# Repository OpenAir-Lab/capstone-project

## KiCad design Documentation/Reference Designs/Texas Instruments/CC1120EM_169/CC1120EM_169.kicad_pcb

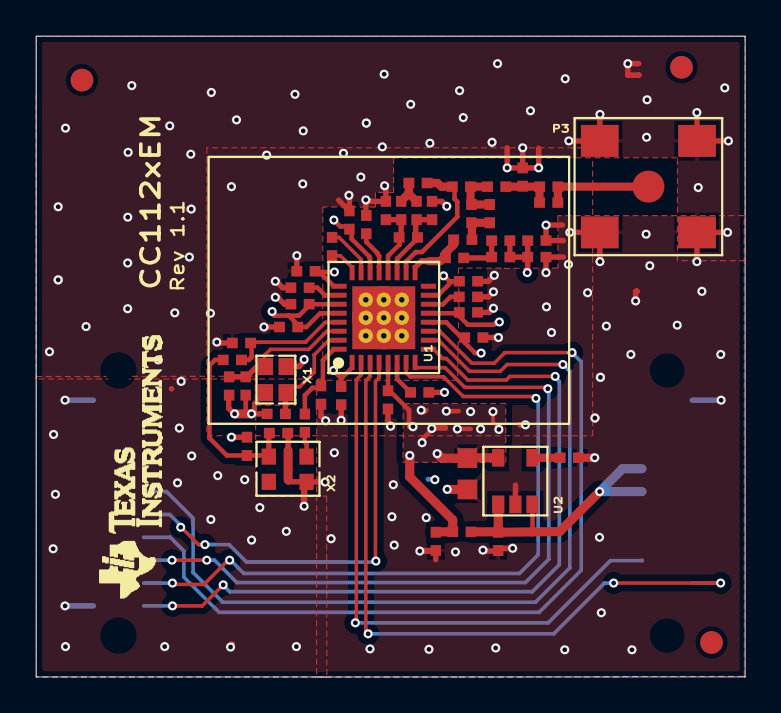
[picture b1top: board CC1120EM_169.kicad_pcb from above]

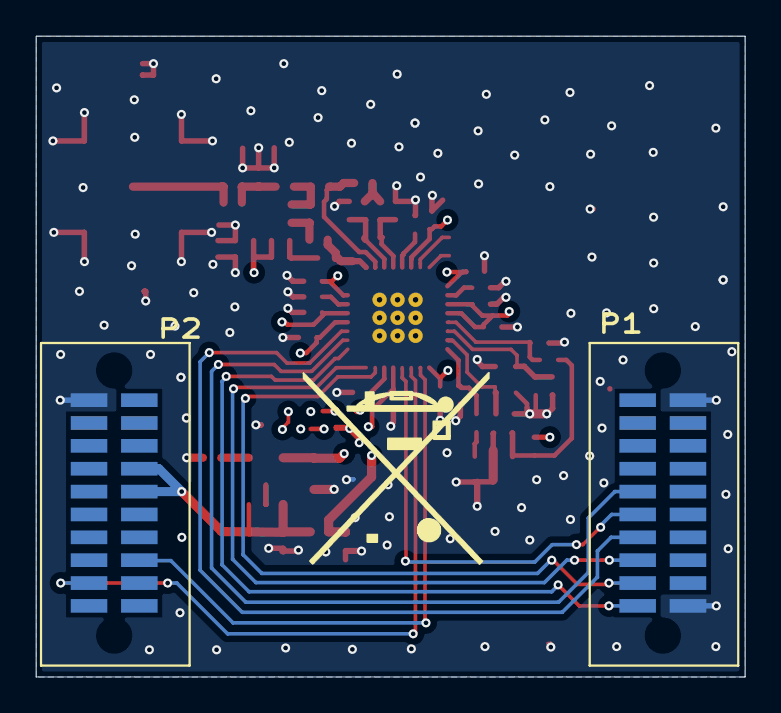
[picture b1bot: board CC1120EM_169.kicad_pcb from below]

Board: 4 copper layers, 39.4 x 35.6 mm, 57 parts (2 on the bottom side), 34 nets.

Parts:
C11, C51, C121, C131, C151, C221, C251, C261, C271, C281, C291: C_47N_0402_X7R_K_25; 0402 (REFLOW LF)
C12, C321: C_100N_0402_X5R_K_10; 0402 (REFLOW LF)
C41, C171, C211: C_10N_0402_X7R_K_25; 0402 (REFLOW LF)
C52: C_2U2_0603_X5R_K_10; 0603 (REFLOW)
C53, C302: C_0402; 0402 (REFLOW LF)
C61: C_220N_0402_X5R_K_10; 0402 (REFLOW LF)
C172, C173: C_100P_0402_NP0_J_50; 0402 (REFLOW LF)
C174: C_82P_0402_NP0_J_50; 0402 (REFLOW LF)
C175, C301, C311: C_15P_0402_NP0_J_50; 0402 (REFLOW LF)
C176, C181, C191, C201: C_12P_0402_NP0_J_50; 0402 (REFLOW LF)
C177: C_1P2_0402_NP0_B_50; 0402 (REFLOW LF)
C231: C_1N8_0402_U2J_J_10; 0402 (REFLOW LF)
C322: C_22P_0402_NP0_J_50; 0402 (REFLOW LF)
FM1, FM2, FM3: FIDUCIAL_MARK; FIDUCAL_MARK
L1: L_BEAD_102_0402; 0402 (REFLOW LF)
L171: L_220N_0402_J; 0402 (REFLOW LF)
L172: L_18N_0402_J_LQW; 0402 (REFLOW LF)
L173: L_100N_0402_J_LQW; 0402 (REFLOW LF)
L174: L_68N_0402_J_LQW; 0402 (REFLOW LF)
L191: L_150N_0402_J; 0402 (REFLOW LF)
L192, L201: L_82N_0402_J_LQW; 0402 (REFLOW LF)
L193: L_39N_0402_J_LQW; 0402 (REFLOW LF)
P1, P2: SMD_SOCKET_2X10; SFM SMD Socket 2x10
P3: SMA_SMD; SMA_SMD (Extended)
R12, R322: R_0_0402; 0402 (REFLOW LF)
R141: R_56K_0402_F; 0402 (REFLOW LF)
R171: R_22_0402_J; 0402 (REFLOW LF)
R321: R_0402; 0402 (REFLOW LF)
U1: CC112X; QFN32_RHM (DATASHEET)
U2: TPS79930; SOT23-5
X1: X_32.000/10/20/60/10; XTAL_SMD_2x1_6 (2.0x1.6mm no paste reduction)
X2: TG_5021CG; TCXO_TG_5021CG (2.5x2mm)

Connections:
3V3A: C12.1, L1.1, P2.7, P2.9, U2.1, U2.3
AGND: C11.1, C12.2, C41.2, C51.1, C52.2, C53.2, C61.2, C121.1, C131.1, C151.1, C171.2, C172.2, C175.2, C201.2, C211.2, C221.2, C251.1, C261.1, C271.1, C281.1, C291.1, C301.1, C302.1, C311.1, C321.1, L192.1, P1.1, P1.19, P2.2, P3.2, P3.3, P3.4, P3.5, R12.1, R141.2, U1.33, U2.2, X1.2, X1.4, X2.2
CSN: P1.14, U1.11
GPIO0: P1.10, U1.10
GPIO2: P1.12, U1.4
GPIO3: P2.18, U1.3
MISO: P1.20, U1.9
MOSI: P1.18, U1.7
unnamed: C41.1, U2.4
unnamed: C173.1, L171.2, R171.1
unnamed: C174.1, C176.1, L172.2
unnamed: C176.2, C181.2, L172.1, L173.2
unnamed: C201.1, L191.2, L201.2, U1.20
unnamed: C211.1, U1.21
unnamed: C231.1, U1.23
unnamed: C301.2, C302.2, U1.30, X1.3
unnamed: C322.1, X2.3
unnamed: C175.1, C177.1, L173.1, L174.2
unnamed: C191.2, L191.1, L192.2, U1.19
unnamed: C181.1, L193.1, U1.18
unnamed: C191.1, L193.2, L201.1
unnamed: C177.2, L174.1, P3.1
unnamed: C322.2, R12.2, U1.32
unnamed: C291.2, R321.2, U1.29
unnamed: C321.2, R321.1, R322.1, X2.4
unnamed: C61.1, U1.6
unnamed: R141.1, U1.14
unnamed: C174.2, L171.1, U1.17
unnamed: C231.2, U1.24
unnamed: C261.2, U1.26
unnamed: C311.2, U1.31, X1.1
RESET: P2.15, U1.2
SCLK: P1.16, U1.8
VDD_REG: C11.2, C51.2, C52.1, C53.1, C121.2, C131.2, C151.2, C171.1, C172.1, C173.2, C221.1, C251.2, C271.2, C281.2, L1.2, R171.2, R322.2, U1.1, U1.5, U1.12, U1.13, U1.15, U1.22, U1.25, U1.27, U1.28, U2.5

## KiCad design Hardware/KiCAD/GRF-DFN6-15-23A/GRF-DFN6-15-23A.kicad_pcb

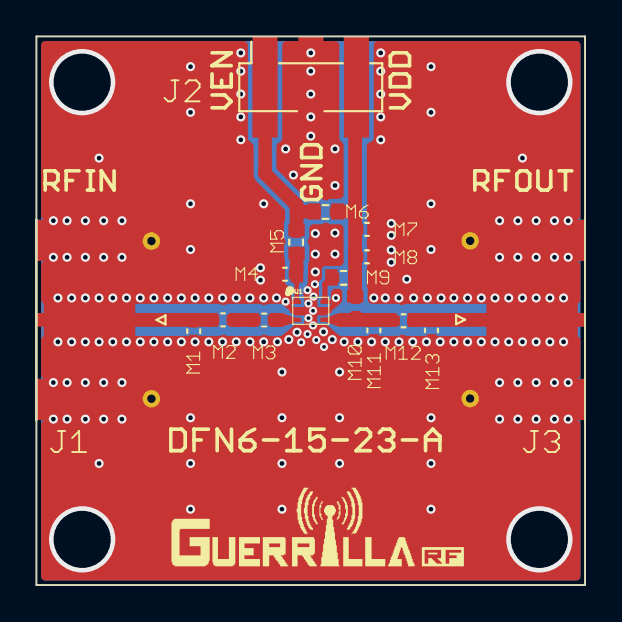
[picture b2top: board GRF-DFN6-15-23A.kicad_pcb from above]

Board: 4 copper layers, 30.5 x 30.5 mm, 21 parts (0 on the bottom side), 10 nets.

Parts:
FID0: GRF_LOCAL_FIDUCIAL; Fiducial_0.5mm_Mask1.5mm
FID@1: GRF_LOCAL_FIDUCIAL; Fiducial_0.5mm_Mask1.5mm
J1: MOLEX_KK_HEADER_3-PIN_0.100-INCH; PinSocket_1x03_P2.54mm_Vertical_SMD_Pin1Right
M1, M11, M13: 0.5pF; C_0402_1005Metric
M2, M3, M4, M12: 100pF; C_0402_1005Metric
M5, M6, M9: 0 Ohm; R_0402_1005Metric
M7, M8: 0.1uF; C_0402_1005Metric
M10: 220nH WW; L_0402_1005Metric
RFIN0: SMA-142-0701-801/806; SMA_Molex_73251-1153_EdgeMount_Horizontal
RFOUT0: SMA-142-0701-801/806; SMA_Molex_73251-1153_EdgeMount_Horizontal
U$1: DFN-6_GENERICUPDATED; SON50P150X150X50-7N-D
U$2, U$3: GRF_LOCAL_FIDUCIAL; Fiducial_0.5mm_Mask1.5mm

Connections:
GND: J1.2, M1.2, M4.2, M7.2, M8.2, M11.2, M13.2, RFIN0.2 (Ext), RFOUT0.2 (Ext), U$1.2 (NC_1), U$1.5 (NC_2), U$1.7 (GND)
unnamed: J1.1, M5.2, M6.1
unnamed: J1.3, M6.2, M7.1, M8.1, M9.2, M10.1
unnamed: M2.2, M3.1
unnamed: M1.1, M2.1, RFIN0.1 (In)
unnamed: M12.1, M13.1, RFOUT0.1 (In)
unnamed: M9.1, U$1.6 (NC_3)
unnamed: M3.2, U$1.3 (RFIN)
unnamed: M10.2, M11.1, M12.2, U$1.4 (RFOUT/VD)
unnamed: M4.1, M5.1, U$1.1 (VEN)

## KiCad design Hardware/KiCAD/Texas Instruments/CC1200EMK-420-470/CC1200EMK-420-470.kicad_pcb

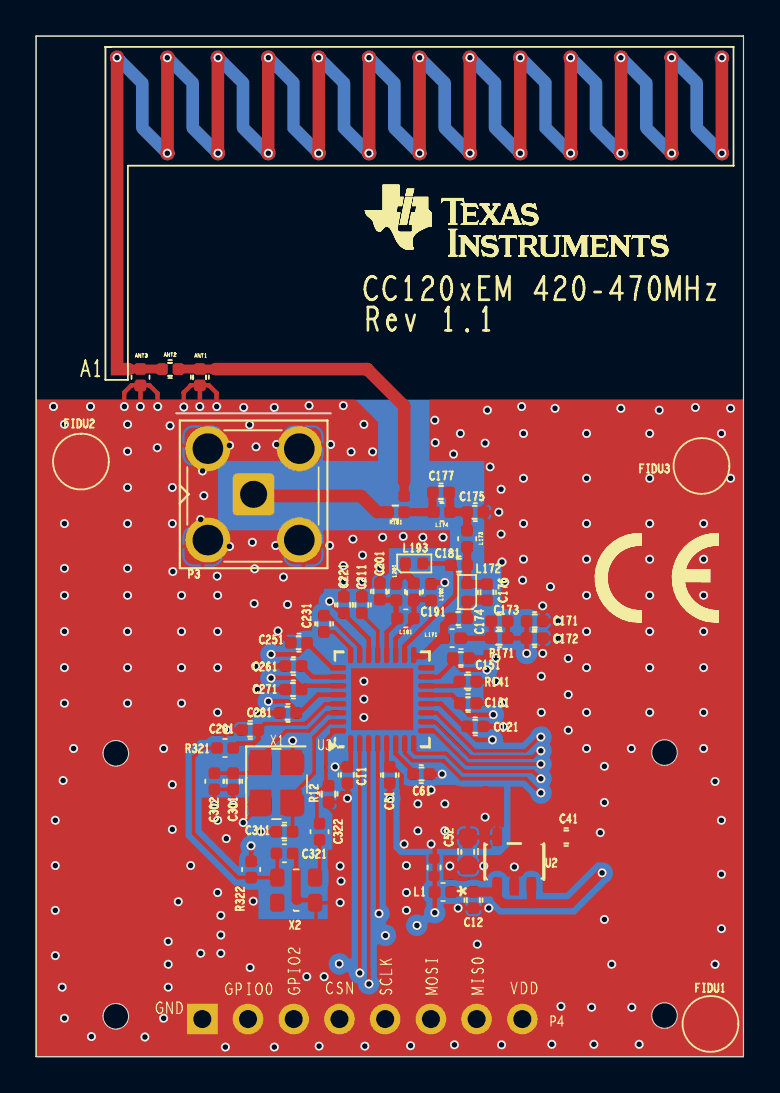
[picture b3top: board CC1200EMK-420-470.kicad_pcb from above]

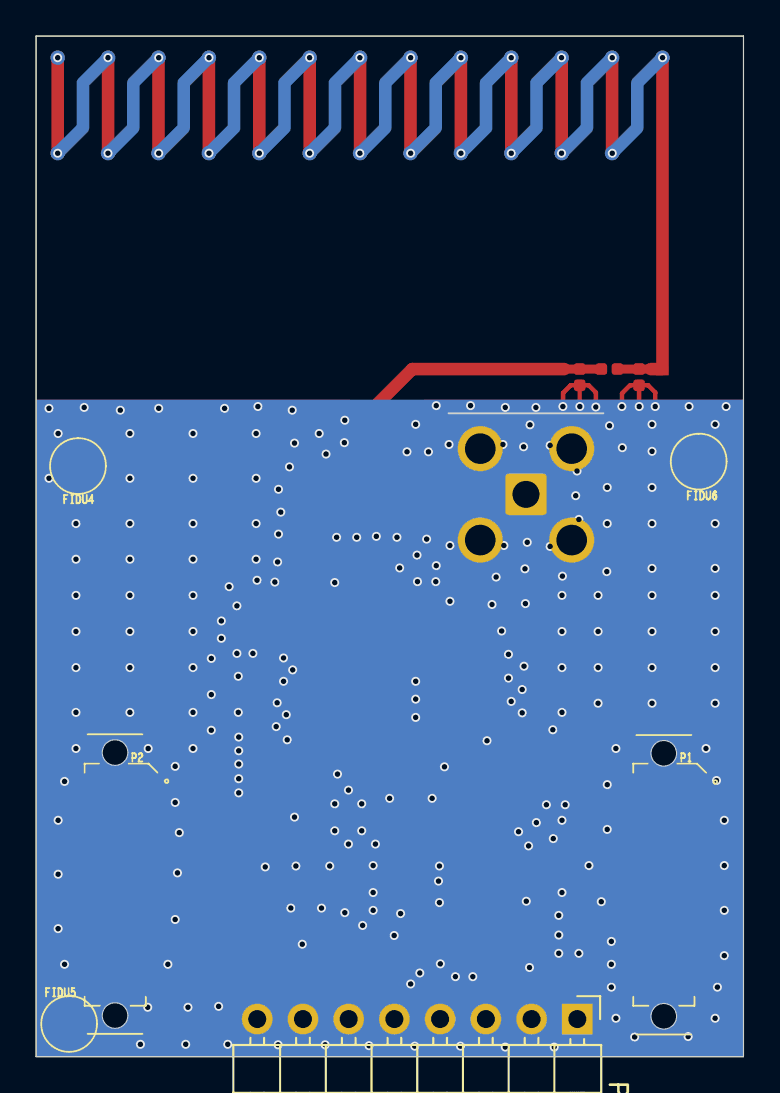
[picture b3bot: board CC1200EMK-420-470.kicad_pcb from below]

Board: 4 copper layers, 39.3 x 56.7 mm, 59 parts (6 on the bottom side), 35 nets.

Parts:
Ant1, Ant2: 0.9p; C_0402_1005Metric
Ant3: 56n; L_0402_1005Metric
C11, C51, C53, C121, C131, C151, C221, C251, C261, C271, C281, C291: 47n; C_0402_1005Metric
C12: 100n; C_0402_1005Metric
C41, C171, C211: 10n; C_0402_1005Metric
C52: 2.2u; C_0402_1005Metric
C61: 220n; C_0402_1005Metric
C172: 100p; C_0402_1005Metric
C173: 56p; C_0402_1005Metric
C174: 39p; C_0402_1005Metric
C175: 6.2p; C_0402_1005Metric
C176: 2.2p; C_0402_1005Metric
C177: 1.2p; C_0402_1005Metric
C181, C191, C201: 5.1p; C_0402_1005Metric
C231: 1.5n; C_0402_1005Metric
C301, C311: 15p; C_0402_1005Metric
FID1, FID2, FID3, FID4, FID5, FID6: Fiducial; Fiducial_1.5mm_Mask3mm
L1: BLM15HG102SN1D; L_0402_1005Metric
L171, L191: 56n; L_0402_1005Metric
L172, L193: 15n; L_0402_1005Metric
L173: 43n; L_0402_1005Metric
L174: 22n; L_0402_1005Metric
L192, L201: 27n; L_0402_1005Metric
P1, P2: SFM-110-02-S-D-A-K-TR; SFM-110-YY-XXX-D-A-K-TR
P3: Conn_Coaxial_UHF; SMA_Amphenol_901-143_Horizontal
P4: Conn_01x08; PinHeader_1x08_P2.54mm_Horizontal
R12: 0R; R_0402_1005Metric
R141: 56k; R_0402_1005Metric
R171, R181: 18; R_0402_1005Metric
U1: TPS79330-EP; DDC5_TEX
U3: CC1200RHBR; QFN-32-1EP_5x5mm_P0.5mm_EP3.45x3.45mm
X1: 40 MHz; Crystal_SMD_3225-4Pin_3.2x2.5mm

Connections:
/CC_GPIO0: P1.10, P4.2, U3.10 (GPIO0)
/CC_GPIO2: P1.12, P4.3, U3.4 (GPIO2)
/CC_GPIO3: P2.18, U3.3 (GPIO3)
/CC_MISO: P1.20, P4.7, U3.9 (SO(GPIO1))
/CC_MOSI: P1.18, P4.6, U3.7 (SI)
/CC_NCS: P1.14, P4.4, U3.11 (~CS)
/CC_NRST: P2.15, U3.2 (~RESET)
/CC_SCLK: P1.16, P4.5, U3.8 (SCLK)
/CC_X1: C301.2, U3.30 (XOSC_Q1), X1.1
/CC_X2: C311.1, U3.31 (XOSC_Q2), X1.3
/LNA_N: C201.1, L191.2, L201.1, U3.20 (LNA_N)
/LNA_P: C191.1, L191.1, L192.1, U3.19 (LNA_P)
/PA: C174.2, L171.2, U3.17 (PA)
/RF_Signal: C177.2, L174.2, R181.2
/TRX_SW: C181.2, L193.1, U3.18 (TRX_SW)
GND: Ant1.2, Ant3.2, C11.2, C12.2, C41.2, C51.2, C52.2, C53.2, C61.2, C121.2, C131.2, C151.2, C171.2, C172.2, C175.2, C201.2, C211.2, C221.2, C251.2, C261.2, C271.2, C281.2, C291.2, C301.1, C311.2, L192.2, P1.1, P1.19, P2.2, P2.20, P3.2 (Ext), P4.1, R12.1, R141.2, U1.2 (GND), U3.33 (GND_EP), X1.2, X1.4
unnamed: Ant1.1, Ant2.1
unnamed: Ant2.2, Ant3.1
unnamed: C173.2, L171.1, R171.2
unnamed: C174.1, C176.2, L172.1
unnamed: C175.1, C177.1, L173.2, L174.1
unnamed: C176.1, C181.1, L172.2, L173.1
unnamed: C191.2, L193.2, L201.2
unnamed: P3.1 (In), R181.1
unnamed: C41.1, U1.4 (FB)
unnamed: C61.1, U3.6 (DCPL)
unnamed: C261.1, U3.26 (DCPL_PFD_CHP)
unnamed: C211.1, U3.21 (DCPL_VCO)
unnamed: C291.1, U3.29 (DCPL_XOSC)
unnamed: R12.2, U3.32 (EXT_XOSC)
unnamed: C231.2, U3.23 (LPF0)
unnamed: C231.1, U3.24 (LPF1)
unnamed: R141.1, U3.14 (RBIAS)
VBUS: C12.1, L1.1, U1.1 (IN), U1.3 (EN)
VDD: C11.1, C51.1, C52.1, C53.1, C121.1, C131.1, C151.1, C171.1, C172.1, C173.1, C221.1, C251.1, C271.1, C281.1, L1.2, P2.7, P2.9, P4.8, R171.1, U1.5 (OUT), U3.1 (VDD_GUARD), U3.5 (DVDD), U3.12 (DVDD), U3.13 (AVDD_IF), U3.15 (AVDD_RF), U3.22 (AVDD_SYNTH1), U3.25 (AVDD_PFD_CHP), U3.27 (AVDD_SYNTH2), U3.28 (AVDD_XOSC)

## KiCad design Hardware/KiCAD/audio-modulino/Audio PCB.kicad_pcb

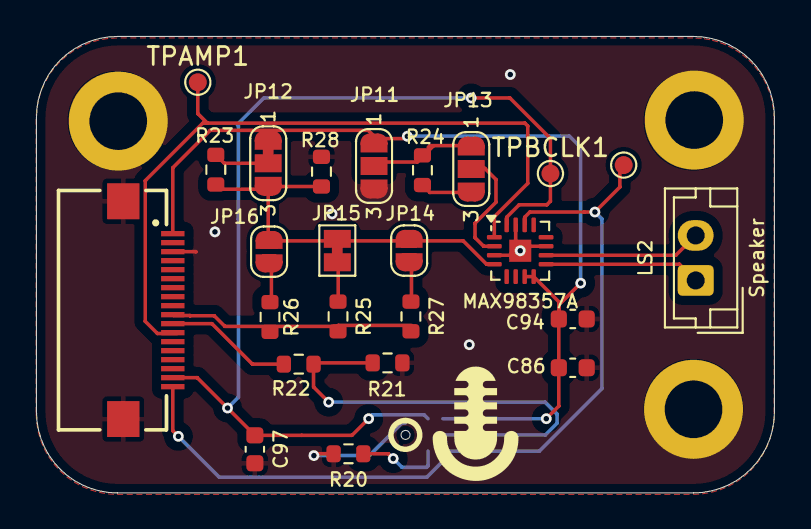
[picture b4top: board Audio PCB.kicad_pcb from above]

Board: 2 copper layers, 41.0 x 25.4 mm, 28 parts (1 on the bottom side), 19 nets.

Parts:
C86: 1uF; C_0603_1608Metric
C94: 0.1uF; C_0603_1608Metric
C97: 22pF; C_0603_1608Metric
H13, H15, H16: M3; MountingHole_3.2mm_M3_ISO14580_Pad
JP11: GAIN_{LOGIC}; SolderJumper-3_P1.3mm_Open_RoundedPad1.0x1.5mm_NumberLabels
JP12: Driver; SolderJumper-3_P1.3mm_Bridged12_RoundedPad1.0x1.5mm_NumberL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
JP13: GAIN_{R}; SolderJumper-3_P1.3mm_Open_RoundedPad1.0x1.5mm_NumberLabels
JP14: CH_LEFT; SolderJumper-2_P1.3mm_Open_RoundedPad1.0x1.5mm
JP15: CH_MONO_MIX; SolderJumper-2_P1.3mm_Bridged_Pad1.0x1.5mm
JP16: CH_RIGHT; SolderJumper-2_P1.3mm_Open_RoundedPad1.0x1.5mm
LS2: Speaker; JST_EH_B2B-EH-A_1x02_P2.50mm_Vertical
MK2: ICS-43434; InvenSense_ICS-43434-6_3.5x2.65mm
R20, R21: 47k; R_0603_1608Metric
R22: 68; R_0603_1608Metric
R23, R27: 2k; R_0603_1608Metric
R24: 100k 5%; R_0603_1608Metric
R25: 634k; R_0603_1608Metric
R26: 330k; R_0603_1608Metric
R28: 100k; R_0603_1608Metric
TPAMP1: TestPoint_Pad_D1.0mm
TPBCLK1: TestPoint_Pad_D1.0mm
TPLRCLK1: TestPoint_Pad_D1.0mm
U7: MAX98357A; TQFN-16-1EP_3x3mm_P0.5mm_EP1.23x1.23mm
X2: EYESPI; Adafruit EYESPI FPC Connector

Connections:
+3.3V: C86.1, C94.1, JP11.1 (A), JP12.1 (A), MK2.5 (VDD), U7.7 (VDD), U7.8 (VDD), X2.1
/AMP_DIN: TPAMP1.1, U7.1 (DIN), X2.12
/Audio Subsystem/GAIN_SLOT: JP13.2 (C), U7.2 (GAIN_SLOT)
/Audio Subsystem/~SD_MODE: JP12.3 (B), JP14.2 (B), JP15.2 (B), JP16.2 (B), R23.2, R28.2, U7.4 (~SD_MODE)
/BCLK: C97.1, MK2.4 (SCK), TPBCLK1.1, U7.16 (BCLK), X2.17
/LRCLK: MK2.1 (WS), TPLRCLK1.1, U7.14 (LRCLK), X2.18
/MIC_DOUT: R22.2, X2.11
/~AMP_SD: R25.2, R26.1, R27.2, X2.10
GND: C86.2, C94.2, C97.2, H13.1, H15.1, H16.1, JP11.3 (B), MK2.3 (GND), R20.2, R21.2, R28.1, U7.3 (GND), U7.11 (GND), U7.15 (GND), U7.17 (PAD), X2.3, X2.Z1, X2.Z2
unnamed: JP11.2 (C), JP13.1 (A), R24.1
unnamed: JP12.2 (C), R23.1
unnamed: JP13.3 (B), R24.2
unnamed: JP14.1 (A), R27.1
unnamed: JP15.1 (A), R25.1
unnamed: JP16.1 (A), R26.2
unnamed: MK2.2 (LR), R20.1
unnamed: MK2.6 (SD), R21.1, R22.1
unnamed: LS2.2, U7.10 (OUTN)
unnamed: LS2.1, U7.9 (OUTP)

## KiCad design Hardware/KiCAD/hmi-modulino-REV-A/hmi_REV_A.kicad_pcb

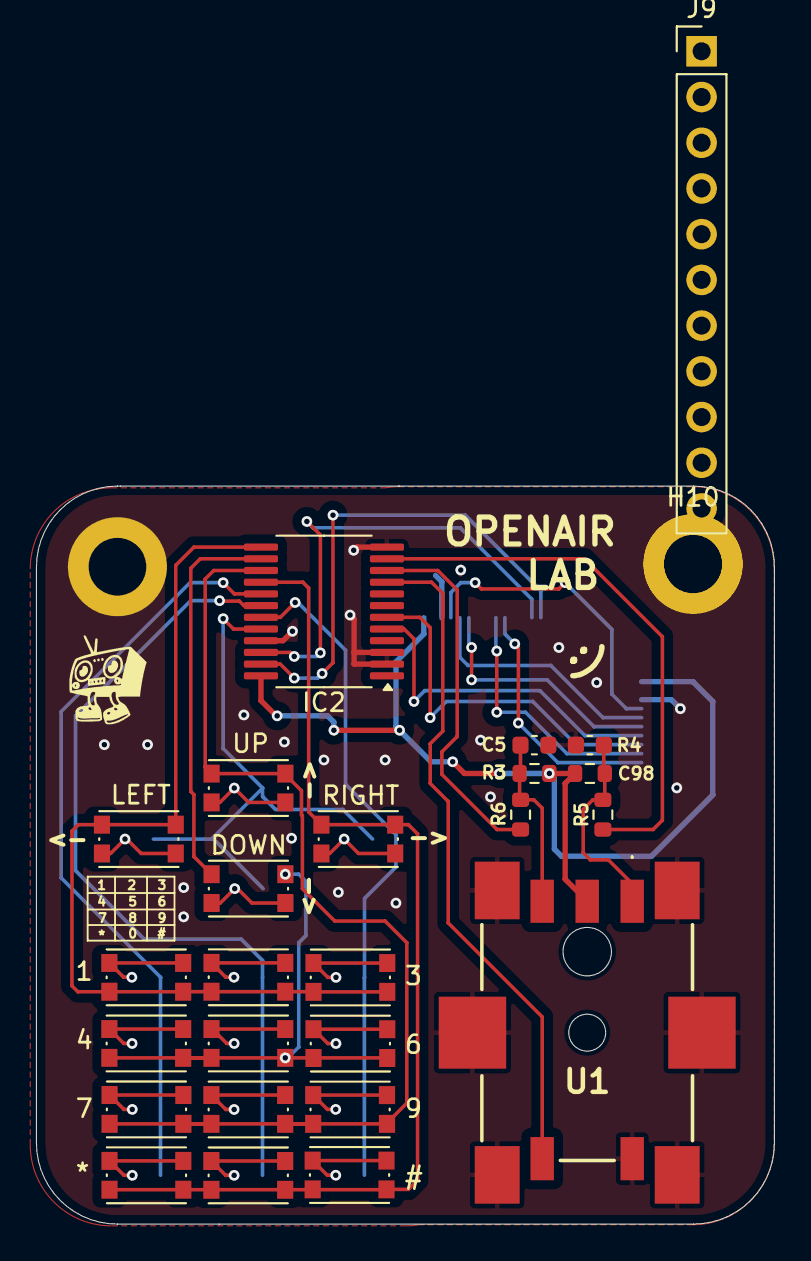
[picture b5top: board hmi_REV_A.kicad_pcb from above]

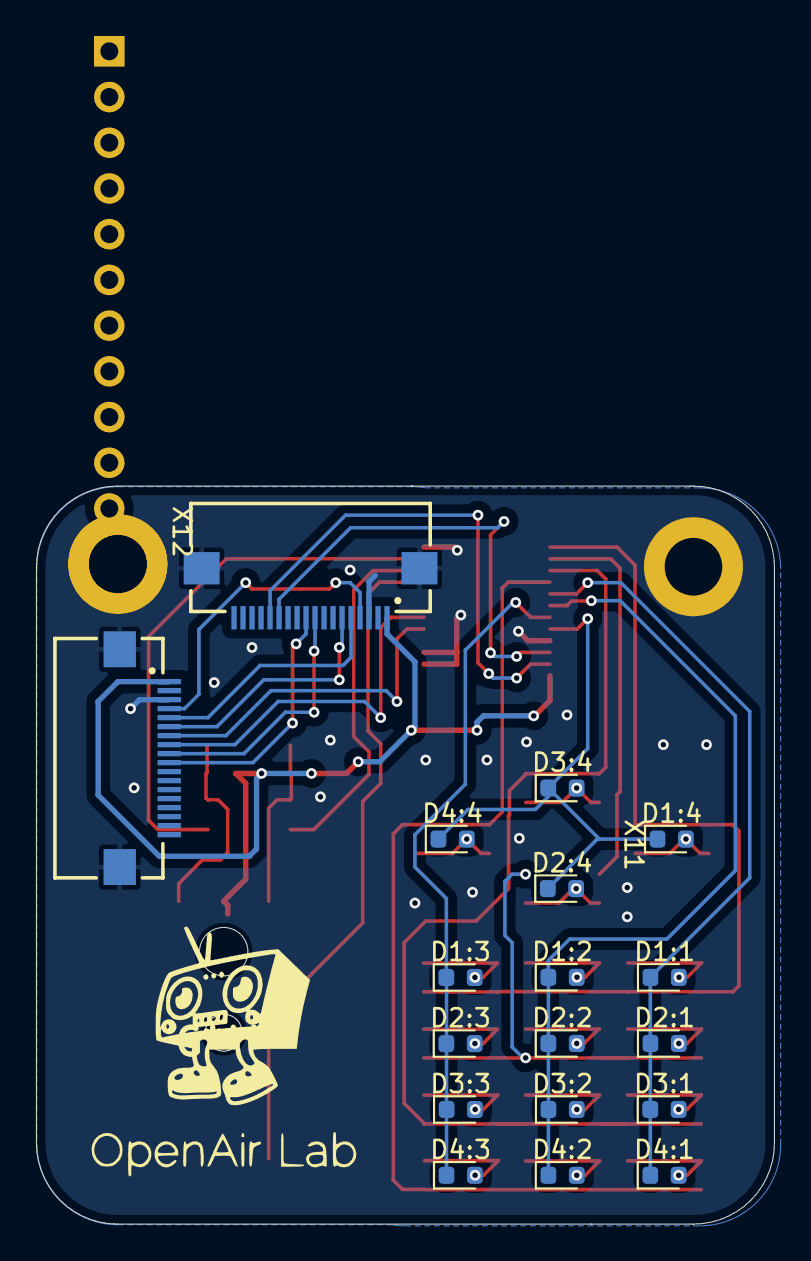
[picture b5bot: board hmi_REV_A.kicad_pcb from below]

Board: 2 copper layers, 41.0 x 41.0 mm, 46 parts (18 on the bottom side), 41 nets.

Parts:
C5, C98: 0.01uF; C_0603_1608Metric
D1:1, D1:2, D1:3, D1:4, D2:1, D2:2, D2:3, D2:4, D3:1, D3:2, D3:3, D3:4, D4:1, D4:2, D4:3, D4:4: D; D_0603_1608Metric
H3, H8, H10: M3; MountingHole_3.2mm_M3_ISO14580_Pad
IC2: PCF8575PWR; SSOP-24_5.3x8.2mm_P0.65mm
J9: Display Pin Socket; PinHeader_1x11_P2.54mm_Vertical
R3, R4, R5, R6: 10k; R_0603_1608Metric
SW30: #; SW_Push_1P1T_NO_CK_KMR2
SW31: 1; SW_Push_1P1T_NO_CK_KMR2
SW32: 4; SW_Push_1P1T_NO_CK_KMR2
SW33: 7; SW_Push_1P1T_NO_CK_KMR2
SW34: 0; SW_Push_1P1T_NO_CK_KMR2
SW35: 2; SW_Push_1P1T_NO_CK_KMR2
SW36: 5; SW_Push_1P1T_NO_CK_KMR2
SW37: 8; SW_Push_1P1T_NO_CK_KMR2
SW38: *; SW_Push_1P1T_NO_CK_KMR2
SW39: 3; SW_Push_1P1T_NO_CK_KMR2
SW40: 6; SW_Push_1P1T_NO_CK_KMR2
SW41: 9; SW_Push_1P1T_NO_CK_KMR2
SW42: RIGHT; SW_Push_1P1T_NO_CK_KMR2
SW43: UP; SW_Push_1P1T_NO_CK_KMR2
SW44: DOWN; SW_Push_1P1T_NO_CK_KMR2
SW45: LEFT; SW_Push_1P1T_NO_CK_KMR2
U1: PEC11J-9215F-S0015; PEC11J9215FS0015
X11, X12: EYESPI; Adafruit EYESPI FPC Connector

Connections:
+3.3V: IC2.24 (VCC), J9.1, J9.2, R3.2, R4.1, U1.C1, X11.1, X12.1
/CARDCS: J9.10, X11.10, X12.10
/Human-Machine Interface/ENC_CLK: IC2.11 (P7), R5.1
/Human-Machine Interface/ENC_DT: IC2.10 (P6), R6.1
/Human-Machine Interface/ENC_SW: IC2.9 (P5), U1.E1 (NO)
/Human-Machine Interface/Keypad/COL1: D1:1.1 (K), D2:1.1 (K), D3:1.1 (K), D4:1.1 (K), IC2.17 (P14)
/Human-Machine Interface/Keypad/COL2: D1:2.1 (K), D2:2.1 (K), D3:2.1 (K), D4:2.1 (K), IC2.18 (P15)
/Human-Machine Interface/Keypad/COL3: D1:3.1 (K), D2:3.1 (K), D3:3.1 (K), D4:3.1 (K), IC2.19 (P16)
/Human-Machine Interface/Keypad/COL4: D1:4.1 (K), D2:4.1 (K), D3:4.1 (K), D4:4.1 (K), IC2.20 (P17)
/Human-Machine Interface/Keypad/ROW1: IC2.13 (P10), SW31.2, SW35.2, SW39.2, SW42.2
/Human-Machine Interface/Keypad/ROW2: IC2.14 (P11), SW32.2, SW36.2, SW40.2, SW43.2
/Human-Machine Interface/Keypad/ROW3: IC2.15 (P12), SW33.2, SW37.2, SW41.2, SW44.2
/Human-Machine Interface/Keypad/ROW4: IC2.16 (P13), SW30.2, SW34.2, SW38.2, SW45.2
/Human-Machine Interface/LITE: J9.11, X12.2
/Human-Machine Interface/TFTDC: IC2.5 (P1), J9.9, X12.7
/Human-Machine Interface/TFTRST: IC2.6 (P2), J9.8, X12.8
/MISO: J9.5, X11.6, X12.6
/MOSI: J9.6, X11.5, X12.5
/SCK: J9.4, X11.4, X12.4
/SCL: IC2.22 (SCL), X11.13
/SDA: IC2.23 (SDA), X11.14
/TFTCS: J9.7, X11.9, X12.9
GND: C5.2, C98.2, H3.1, H8.1, H10.1, IC2.2 (A1), IC2.3 (A2), IC2.12 (GND), IC2.21 (A0), J9.3, U1.D1 (COM), U1.MP1, U1.MP2, U1.MP3, U1.MP4, U1.MP5, U1.MP6, X11.3, X11.Z1, X11.Z2, X12.3, X12.Z1, X12.Z2
unnamed: C5.1, R3.1, R6.2, U1.B1
unnamed: C98.1, R4.2, R5.2, U1.A1
unnamed: D1:1.2 (A), SW31.1
unnamed: D1:2.2 (A), SW35.1
unnamed: D1:3.2 (A), SW39.1
unnamed: D1:4.2 (A), SW42.1
unnamed: D2:1.2 (A), SW32.1
unnamed: D2:2.2 (A), SW36.1
unnamed: D2:3.2 (A), SW40.1
unnamed: D2:4.2 (A), SW43.1
unnamed: D3:1.2 (A), SW33.1
unnamed: D3:2.2 (A), SW37.1
unnamed: D3:3.2 (A), SW41.1
unnamed: D3:4.2 (A), SW44.1
unnamed: D4:1.2 (A), SW30.1
unnamed: D4:2.2 (A), SW34.1
unnamed: D4:3.2 (A), SW38.1
unnamed: D4:4.2 (A), SW45.1
